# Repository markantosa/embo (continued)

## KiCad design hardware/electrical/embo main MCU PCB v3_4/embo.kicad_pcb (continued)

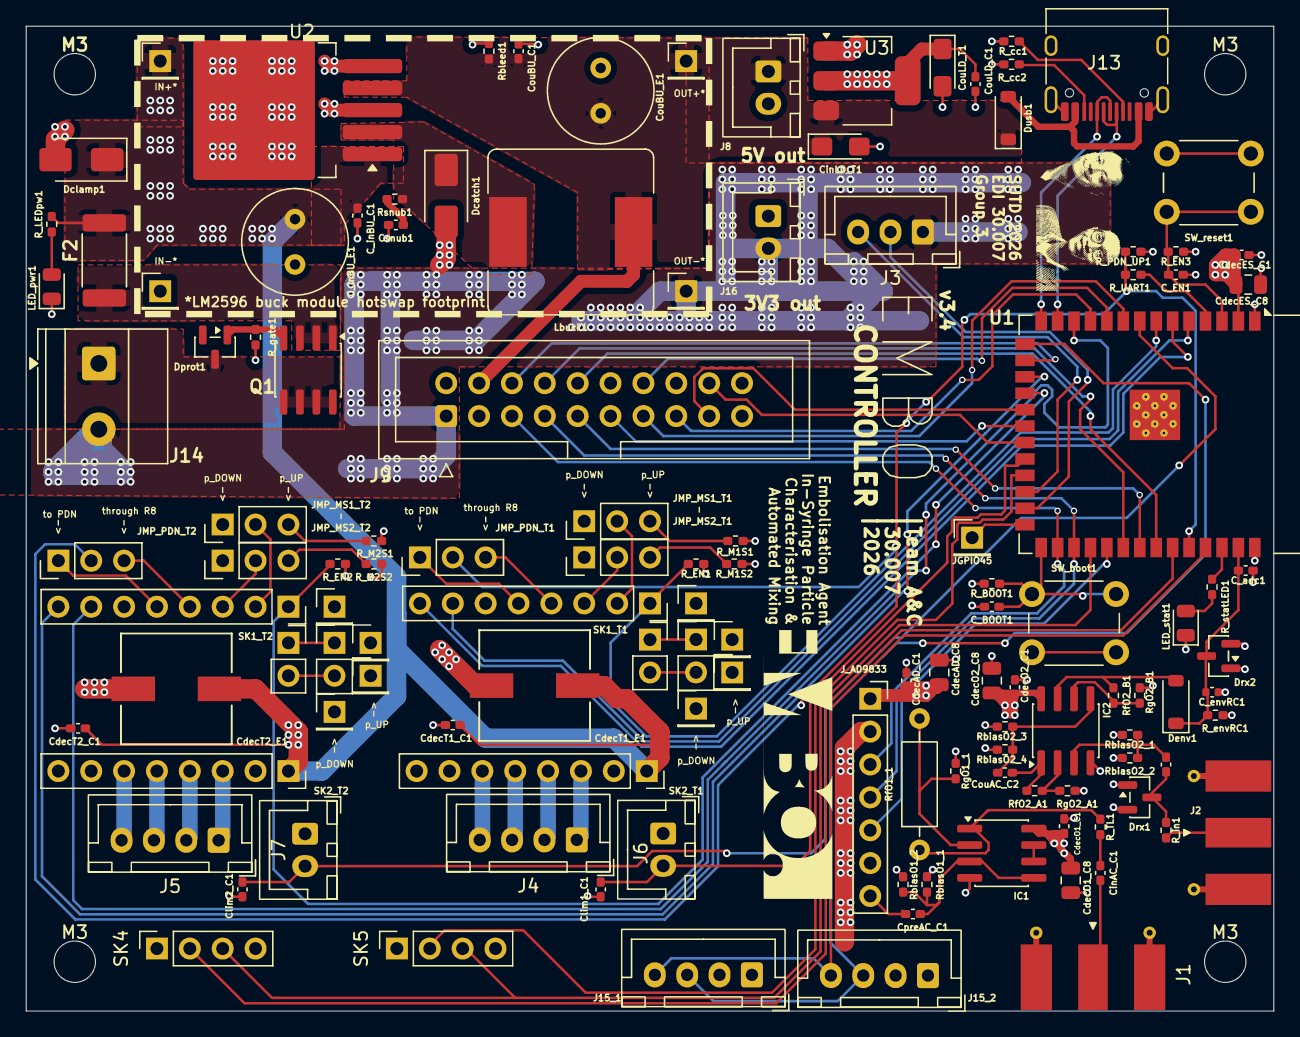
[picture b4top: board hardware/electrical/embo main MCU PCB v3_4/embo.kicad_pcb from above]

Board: 4 copper layers, 96.4 x 76.1 mm, 125 parts (0 on the bottom side), 90 nets.

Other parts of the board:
M3, M3#2, M3#3, M3#4: MountingHole_3.2mm_M3

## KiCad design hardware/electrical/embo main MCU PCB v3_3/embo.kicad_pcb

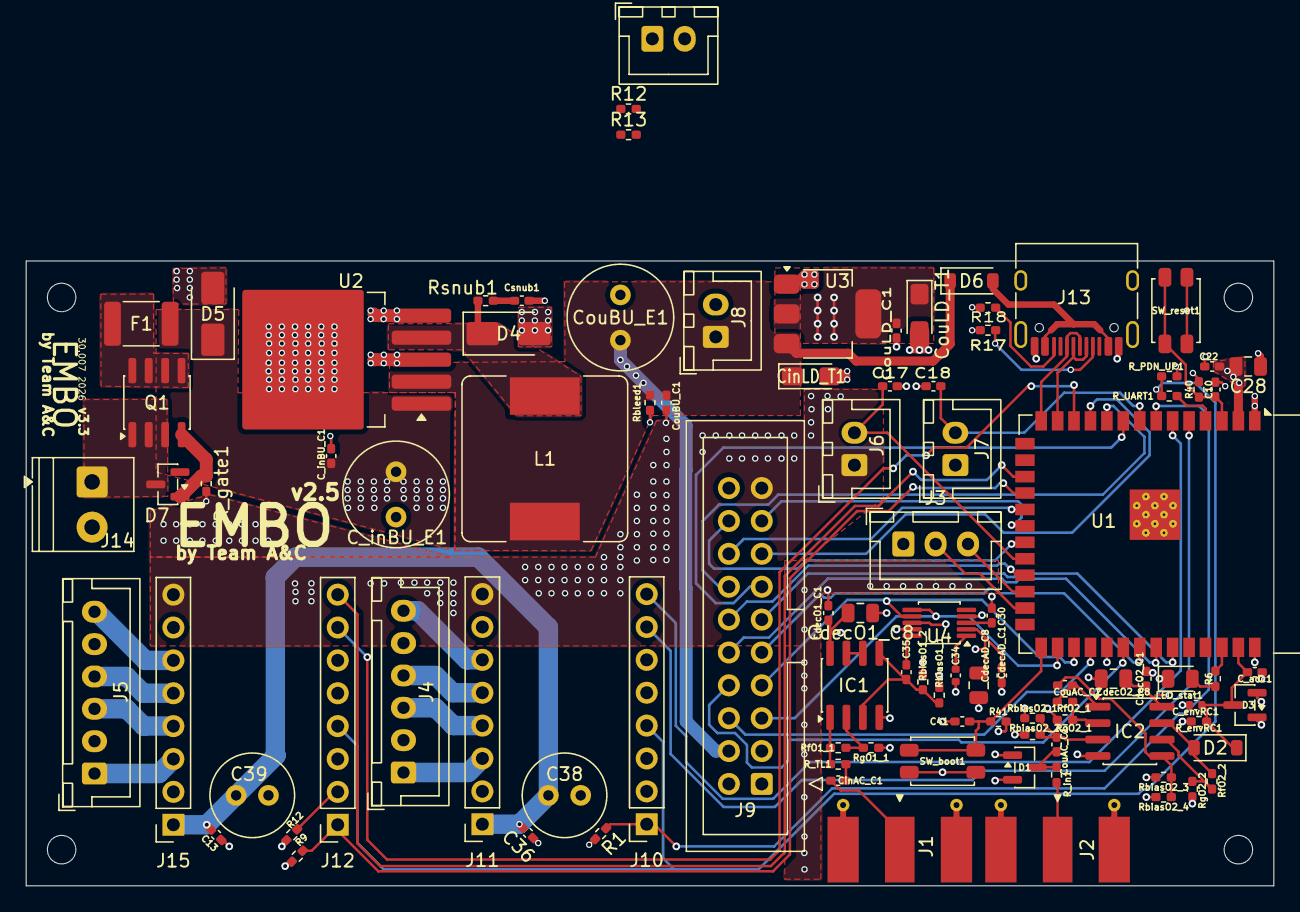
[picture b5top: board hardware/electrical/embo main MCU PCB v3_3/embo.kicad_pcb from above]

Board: 4 copper layers, 96.4 x 48.3 mm, 97 parts (0 on the bottom side), 72 nets.

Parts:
C10: 1µF X7R; C_0402_1005Metric_Pad0.74x0.62mm_HandSolder
C13, C17, C18, C22, C30, C35, C36, C41: 100nF X7R; C_0402_1005Metric_Pad0.74x0.62mm_HandSolder
C28: 10µF X5R 0805; C_0805_2012Metric
C34: 10nF X7R; C_0402_1005Metric
C38, C39: 100µF 35V electrolytic radial; C_Radial_D6.3mm_H7.0mm_P2.50mm
C_adc1: 100nF X7R; C_0402_1005Metric_Pad0.74x0.62mm_HandSolder
C_envRC1: 10nF X7R; C_0402_1005Metric
C_inBU_C1: 100nF X7R; C_0402_1005Metric_Pad0.74x0.62mm_HandSolder
C_inBU_E1: 100 µF 50 V radial; C_Radial_D8.0mm_H11.5mm_P3.50mm
CdecAD_C1: 100nF X7R; C_0402_1005Metric_Pad0.74x0.62mm_HandSolder
CdecAD_C8: 10µF X5R 0805; C_0805_2012Metric
CdecO1_C1, CdecO2_C1: 100nF X7R; C_0402_1005Metric_Pad0.74x0.62mm_HandSolder
CdecO1_C8, CdecO2_C8: 10µF X5R 0805; C_0805_2012Metric
CinAC_C1: 100nF X7R; C_0402_1005Metric_Pad0.74x0.62mm_HandSolder
CinLD_T1: 10µF 10V tantalum Case A; CP_EIA-3216-18_Kemet-A_HandSolder
CouAC_C1, CouAC_C2: 100nF X7R; C_0402_1005Metric_Pad0.74x0.62mm_HandSolder
CouBU_C1: 100nF X7R; C_0402_1005Metric_Pad0.74x0.62mm_HandSolder
CouBU_E1: 220µF 10V low-ESR electrolytic radial; C_Radial_D8.0mm_H11.5mm_P3.50mm
CouLD_C1: 100nF X7R; C_0402_1005Metric_Pad0.74x0.62mm_HandSolder
CouLD_T1: 10µF 10V tantalum Case A; CP_EIA-3216-18_Kemet-A_HandSolder
Csnub1: 1nF X7R; C_0402_1005Metric_Pad0.74x0.62mm_HandSolder
D1, D3: BAV99; SOT-23
D2: BAT54; D_SOD-123
D4: SS34A; D_SMA
D5: SMBJ28A; D_SMA
D6: 1N5819; D_SOD-123
D7: BZX84C15, 15 V Zener, SOT-23; SOT-23
F1: 5A littlefuse; Fuse_1812_4532Metric_Pad1.30x3.40mm_HandSolder
IC1, IC2: OPA2354; SOIC-8_3.9x4.9mm_P1.27mm
J1, J2: Conn_Coaxial; SMA_Molex_73251-1153_EdgeMount_Horizontal
J3: UART to RPi; JST_XH_B3B-XH-A_1x03_P2.50mm_Vertical
J4: JSTXH 6pin Socket 1; JST_XH_B6B-XH-A_1x06_P2.50mm_Vertical
J5: JSTXH 6pin Socket 2; JST_XH_B6B-XH-A_1x06_P2.50mm_Vertical
J6: motor 1; JST_XH_B2B-XH-A_1x02_P2.50mm_Vertical
J7: motor 2; JST_XH_B2B-XH-A_1x02_P2.50mm_Vertical
J8: 5V out; JST_XH_B2B-XH-A_1x02_P2.50mm_Vertical
J8#2: LED Panel; JST_XH_B2B-XH-A_1x02_P2.50mm_Vertical
J9: Conn_02x10_Odd_Even; IDC-Header_2x10_P2.54mm_Vertical
J10, J11, J12, J15: Conn_01x08; PinSocket_1x08_P2.54mm_Vertical
J13: USB_C_Receptacle_USB2.0_16P; USB_C_Receptacle_HRO_TYPE-C-31-M-12
J14: 24 V PSU input; TerminalBlock_Phoenix_PT-1,5-2-3.5-H_1x02_P3.50mm_Horizontal
L1: 100µH; L_Bourns_SRR1260
LED_stat1: green LED; LED_0805_2012Metric
Q1: AO4407A; SOIC-8_3.9x4.9mm_P1.27mm
R1, R9, R12, R12#2, R13: 10kΩ; R_0402_1005Metric_Pad0.72x0.64mm_HandSolder
R6: 330Ω; R_0402_1005Metric_Pad0.72x0.64mm_HandSolder
R17, R18: 5.1kΩ; R_0402_1005Metric_Pad0.72x0.64mm_HandSolder
R40, R41: 10kΩ 0402; R_0402_1005Metric_Pad0.72x0.64mm_HandSolder
R_PDN_UP1: 10kΩ 0402; R_0402_1005Metric_Pad0.72x0.64mm_HandSolder
R_TL1: 47Ω; R_0402_1005Metric_Pad0.72x0.64mm_HandSolder
R_UART1: 1kΩ 0402; R_0402_1005Metric_Pad0.72x0.64mm_HandSolder
R_envRC1: 10kΩ 0402; R_0402_1005Metric_Pad0.72x0.64mm_HandSolder
R_gate1: 10 kΩ 0402; R_0402_1005Metric_Pad0.72x0.64mm_HandSolder
R_in1: 100Ω 0402; R_0402_1005Metric_Pad0.72x0.64mm_HandSolder
RbiasO1_1, RbiasO1_2, RbiasO2_1, RbiasO2_2, RbiasO2_3, RbiasO2_4: 10kΩ; R_0402_1005Metric_Pad0.72x0.64mm_HandSolder
Rbleed1: 4.7kΩ; R_0402_1005Metric_Pad0.72x0.64mm_HandSolder
RfO1_1: 390Ω; R_0402_1005Metric_Pad0.72x0.64mm_HandSolder
RfO2_1, RfO2_2: 910Ω; R_0402_1005Metric_Pad0.72x0.64mm_HandSolder
RgO1_1, RgO2_1, RgO2_2: 100Ω; R_0402_1005Metric_Pad0.72x0.64mm_HandSolder
Rsnub1: 10kΩ; R_0402_1005Metric_Pad0.72x0.64mm_HandSolder
SW_boot1: 6×6mm tactile; SW_SPST_EVQP2_MiddlePushTravel_H2.5mm
SW_reset1: 6×6mm tactile; SW_SPST_EVQP2_MiddlePushTravel_H2.5mm
U1: ESP32-S3-WROOM-1
U2: LM2596S-5; TO-263-5_TabPin3
U3: AMS1117-3.3; SOT-223-3_TabPin2
U4: AD9833xRM; MSOP-10_3x3mm_P0.5mm

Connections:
+3V3: C22.2, C28.2, CdecAD_C1.1, CdecAD_C8.2, CdecO1_C1.1, CdecO1_C8.1, CdecO2_C1.1, CdecO2_C8.1, CouLD_C1.1, CouLD_T1.1, D1.2 (A), D3.2 (A), IC1.8 (V+), IC2.8 (V+), J9.2, J11.7, J15.7, R1.1, R9.1, R12.1, R12#2.1, R13.1, R40.2, R41.2, R_PDN_UP1.2, RbiasO1_1.1, RbiasO2_1.1, RbiasO2_3.1, U1.2 (3V3), U3.2 (VO), U4.2 (VDD)
+5V: CinLD_T1.1, CouBU_C1.1, CouBU_E1.1, D6.1 (K), J8.1, J8#2.1, J9.4, L1.1, Rbleed1.1, U2.4 (FB), U3.3 (VI)
+24V: C13.1, C36.1, C38.1, C39.1, C_inBU_C1.1, C_inBU_E1.1, D5.1 (K), F1.2, J11.1, J15.1, U2.1 (VIN)
/AD9833_SC: U1.31 (IO38), U4.8 (~FSYNC)
/BTN1: J9.16, U1.19 (IO11)
/BTN2: J9.17, U1.20 (IO12)
/BUZ_PWM: J9.18, U1.21 (IO13)
/EC11_A (CLK): J9.13, U1.9 (IO16)
/EC11_B (DT): J9.14, U1.10 (IO17)
/EC11_SW: J9.15, U1.11 (IO18)
/LIMIT_M1: C17.1, J6.2, U1.22 (IO14)
/LIMIT_M2: C18.1, J7.2, U1.8 (IO15)
/M1_A1: J4.3, J11.4
/M1_A2: J4.1, J11.3
/M1_B1: J4.4, J11.5
/M1_B2: J4.6, J11.6
/M1_DIR: J10.8, U1.6 (IO6)
/M1_EN: J10.1, R1.2, U1.7 (IO7)
/M1_STEP: J10.7, U1.5 (IO5)
/M2_A1: J5.3, J15.4
/M2_A2: J5.1, J15.3
/M2_B1: J5.4, J15.5
/M2_B2: J5.6, J15.6
/M2_DIR: J12.8, U1.17 (IO9)
/M2_EN: J12.1, R9.2, U1.18 (IO10)
/M2_STEP: J12.7, U1.12 (IO8)
/RX_AMP_IN: CouAC_C1.1, D1.3 (K), R_in1.2
/SPI_CLK: J9.7, U1.29 (IO36), U4.7 (SCLK)
/SPI_MISO: J9.6, U1.30 (IO37)
/SPI_MOSI: J9.5, U1.28 (IO35), U4.6 (SDATA)
/STAGE1_OUT: CouAC_C2.1, IC2.1 (OUTA), RfO2_1.2
/TFT_CS: J9.8, U1.32 (IO39)
/TFT_DC: J9.9, U1.33 (IO40)
/TFT_RST: J9.10, U1.34 (IO41)
/TMC_UART: R_UART1.2, U1.4 (IO4)
/TOUCH_CS: J9.11, U1.35 (IO42)
/TOUCH_IRQ: J9.12, U1.23 (IO21)
/TX_AMP_IN: C35.1, U4.10 (VOUT)
/TX_OUT: CinAC_C1.2, J1.1 (In)
/UART_RX: J3.2, U1.25 (IO48)
/UART_TX: J3.3, U1.24 (IO47)
/UAS_ADC: C_adc1.1, C_envRC1.1, D2.1 (K), D3.3 (K), R_envRC1.1, U1.39 (IO1)
/USB_D+: J13.A6 (D+), J13.B6 (D+), U1.14 (USB_D+)
/USB_D-: J13.A7 (D-), J13.B7 (D-), U1.13 (USB_D-)
/status_LED: R6.2, U1.38 (IO2)
GND: C10.2, C13.2, C17.2, C18.2, C22.1, C28.1, C30.2, C34.1, C36.2, C38.2, C39.2, C41.2, C_adc1.2, C_envRC1.2, C_inBU_C1.2, C_inBU_E1.2, CdecAD_C1.2, CdecAD_C8.1, CdecO1_C1.2, CdecO1_C8.2, CdecO2_C1.2, CdecO2_C8.2, CinLD_T1.2, CouBU_C1.2, CouBU_E1.2, CouLD_C1.2, CouLD_T1.2, Csnub1.2, D1.1 (K), D3.1 (K), D4.2 (A), D5.2 (A), IC1.4 (V-), IC2.4 (V-), J1.2 (Ext), J2.2 (Ext), J3.1, J6.1, J7.1, J8.2, J8#2.2, J9.1, J9.3, J9.19, J10.3, J10.6, J11.2, J11.8, J12.3, J12.6, J13.A1 (GND), J13.A12 (GND), J13.B1 (GND), J13.B12 (GND), J13.SH (SHIELD), J14.2, J15.2, J15.8, LED_stat1.1 (K), R17.2, R18.2, R_envRC1.2, R_gate1.2, RbiasO1_2.2, RbiasO2_2.2, RbiasO2_4.2, Rbleed1.2, RgO1_1.1, RgO2_1.1, RgO2_2.2, SW_boot1.2, SW_reset1.2, U1.1 (GND), U1.40 (GND), U1.41 (GND), U2.3 (GND), U2.5 (~ON/OFF), U3.1 (GND), U4.4 (DGND), U4.9 (AGND)
unnamed: CinAC_C1.1, R_TL1.2
unnamed: Csnub1.1, Rsnub1.2
unnamed: D2.2 (A), IC2.7 (OUTB), RfO2_2.2
unnamed: D4.1 (K), L1.2, Rsnub1.1, U2.2 (OUT)
unnamed: D6.2 (A), J13.A4 (VBUS), J13.A9 (VBUS), J13.B4 (VBUS), J13.B9 (VBUS)
unnamed: D7.1 (A), Q1.4, R_gate1.1
unnamed: D7.3 (K), J14.1, Q1.5, Q1.6, Q1.7, Q1.8
unnamed: F1.1, Q1.1, Q1.2, Q1.3
unnamed: C35.2, IC1.3 (+INA), IC1.5 (+INB), RbiasO1_1.2, RbiasO1_2.1
unnamed: IC1.2 (-INA), RfO1_1.2, RgO1_1.2
unnamed: IC1.6 (-INB), IC1.7 (OUTB)
unnamed: IC1.1 (OUTA), R_TL1.1, RfO1_1.1
unnamed: CouAC_C1.2, IC2.3 (+INA), RbiasO2_1.2, RbiasO2_2.1
unnamed: CouAC_C2.2, IC2.5 (+INB), RbiasO2_3.2, RbiasO2_4.1
unnamed: IC2.2 (-INA), RfO2_1.1, RgO2_1.2
unnamed: IC2.6 (-INB), RfO2_2.1, RgO2_2.1
unnamed: J2.1 (In), R_in1.1
unnamed: J12.2, R12#2.2
unnamed: J13.A5 (CC1), R17.1
unnamed: J13.B5 (CC2), R18.1
unnamed: R_PDN_UP1.1, R_UART1.1
unnamed: LED_stat1.2 (A), R6.1
unnamed: C10.1, R40.1, SW_reset1.1, U1.3 (EN)
unnamed: C41.1, R41.1, SW_boot1.1, U1.27 (IO0)
unnamed: C30.1, U4.3 (CAP/2.5V)
unnamed: C34.2, U4.1 (COMP)

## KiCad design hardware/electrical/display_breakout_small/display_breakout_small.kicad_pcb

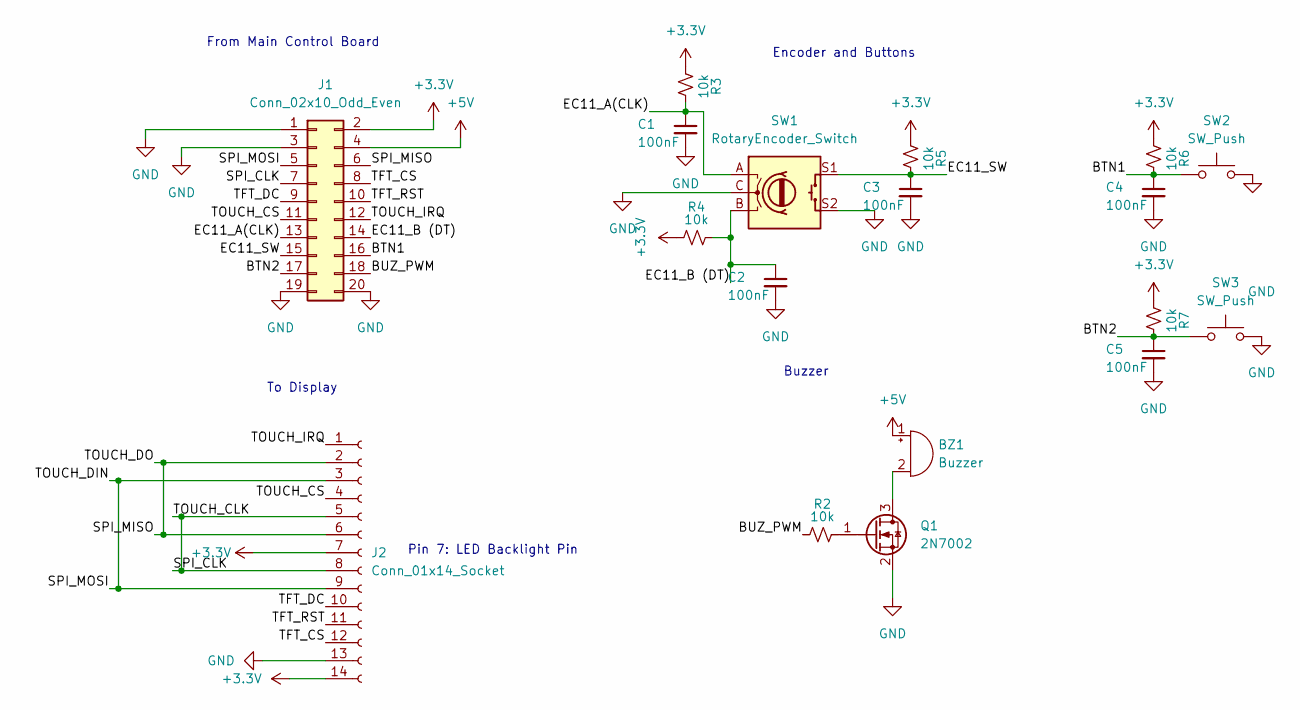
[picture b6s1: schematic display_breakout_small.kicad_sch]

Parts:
BZ1: Buzzer; Buzzer_12x9.5RM7.6
C1, C2, C3, C4, C5: 100nF; C_0402_1005Metric_Pad0.74x0.62mm_HandSolder
J1: Conn_02x10_Odd_Even; IDC-Header_2x10_P2.54mm_Vertical
J2: Conn_01x14_Socket; PinSocket_1x14_P2.54mm_Vertical
Q1: 2N7002; SOT-23
R2, R3, R4, R5, R6, R7: 10k; R_0402_1005Metric_Pad0.72x0.64mm_HandSolder
SW1: RotaryEncoder_Switch; RotaryEncoder_Alps_EC11E-Switch_Vertical_H20mm
SW2, SW3: SW_Push; SW_TH_Tactile_Omron_B3F-100x

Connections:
+3.3V: J1.2, J2.7, J2.14, R3.2, R4.2, R5.2, R6.2, R7.2
+5V: BZ1.1 (+), J1.4
/BTN1: C4.1, J1.16, R6.1, SW2.1
/BTN2: C5.1, J1.17, R7.1, SW3.1
/BUZ_PWM: J1.18, R2.2
/EC11_A(CLK): C1.1, J1.13, R3.1, SW1.A
/EC11_B (DT): C2.1, J1.14, R4.1, SW1.B
/EC11_SW: C3.1, J1.15, R5.1, SW1.S1
/SPI_CLK: J1.7, J2.5, J2.8
/SPI_MISO: J1.6, J2.2, J2.6
/SPI_MOSI: J1.5, J2.3, J2.9
/TFT_CS: J1.8, J2.12
/TFT_DC: J1.9, J2.10
/TFT_RST: J1.10, J2.11
/TOUCH_CS: J1.11, J2.4
/TOUCH_IRQ: J1.12, J2.1
GND: C1.2, C2.2, C3.2, C4.2, C5.2, J1.1, J1.3, J1.19, J1.20, J2.13, Q1.2 (S), SW1.C, SW1.S2, SW2.2, SW3.2
unnamed: BZ1.2 (-), Q1.3 (D)
unnamed: Q1.1 (G), R2.1

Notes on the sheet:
Buzzer
From Main Control Board
Encoder and Buttons
Pin 7: LED Backlight Pin
To Display

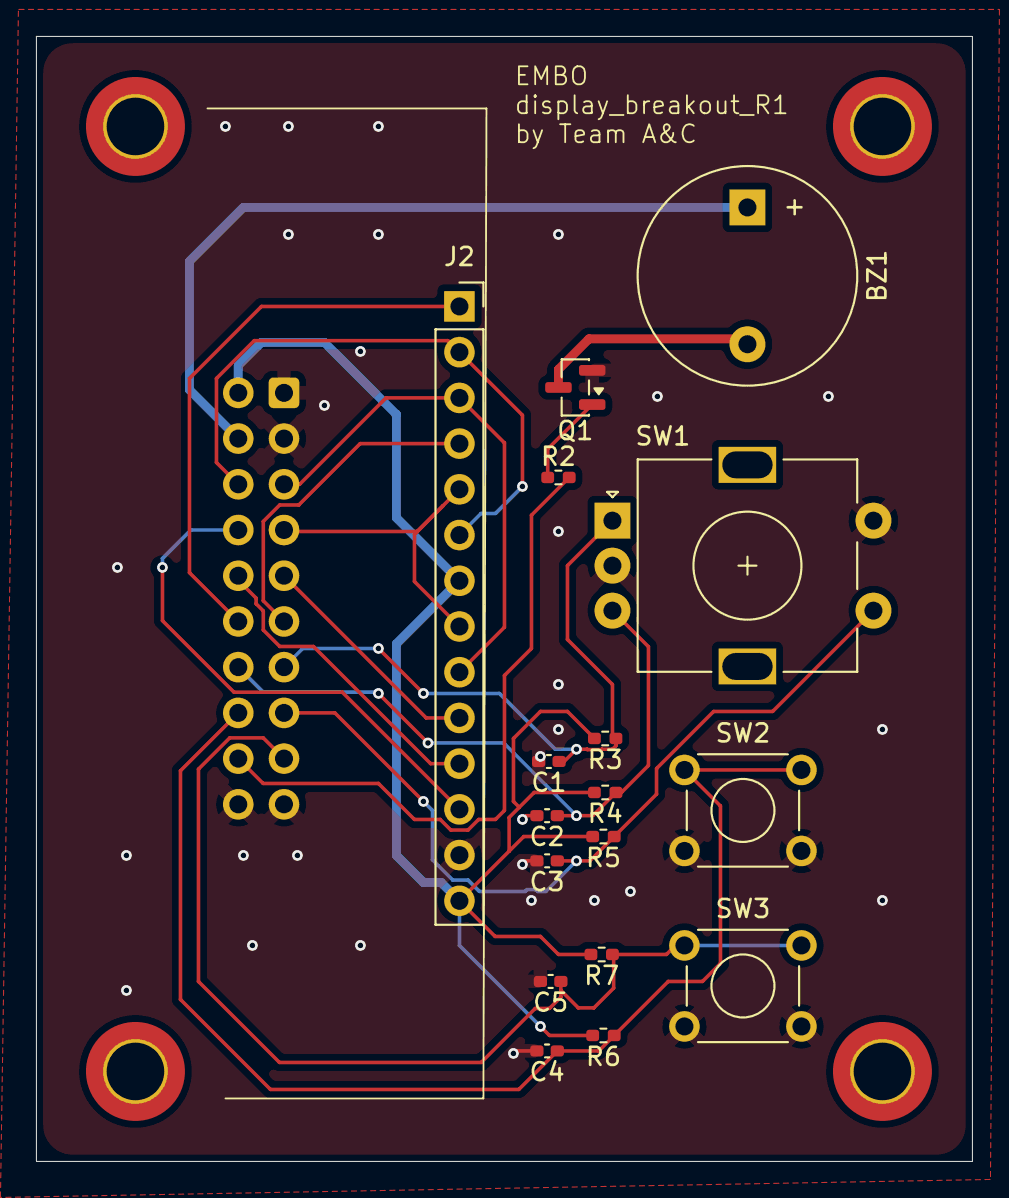
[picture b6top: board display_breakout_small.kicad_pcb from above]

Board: 2 copper layers, 52.0 x 62.5 mm, 18 parts (1 on the bottom side), 19 nets.

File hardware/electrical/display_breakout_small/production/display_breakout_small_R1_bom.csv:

Designator,Footprint,Quantity,Value,LCSC Part #
BZ1,Buzzer_12x9.5RM7.6,1,Buzzer,
"C1, C2, C3, C4, C5",0402,5,100nF,
J1,IDC-Header_2x10_P2.54mm_Vertical,1,Conn_02x10_Odd_Even,
J2,PinSocket_1x14_P2.54mm_Vertical,1,Conn_01x14_Socket,
Q1,SOT-23,1,2N7002,
"R2, R3, R4, R5, R6, R7",0402,6,10k,
SW1,RotaryEncoder_Alps_EC11E-Switch_Vertical_H20mm,1,RotaryEncoder_Switch,
"SW2, SW3",SW_TH_Tactile_Omron_B3F-100x,2,SW_Push,

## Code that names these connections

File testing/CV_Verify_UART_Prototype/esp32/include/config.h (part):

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// now two separate pins (GPIO4 TX / GPIO44 RX), not one bidirectional pin.

// UAS / ADC
#define PIN_UAS_ADC         1   // ADC1_CH0 — envelope detector output

// Status LED
#define PIN_STATUS_LED      2

// I2C turbidity bus — APDS9960 (0x39, ALS) + MAX30102 (0x57, backscatter)
#define PIN_I2C_SDA         3
#define PIN_I2C_SCL         43
#define I2C_CLOCK_HZ        400000
#define APDS9960_ADDR       0x39
#define MAX30102_ADDR       0x57
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#define TURBIDITY_REINIT_INTERVAL_MS  2000

// Motor driver — shared PDN_UART bus, genuinely separate TX/RX pins
#define PIN_TMC_UART_TX     4
#define PIN_TMC_UART_RX     44

// Motor 1 (TMC2209 U5/SK1, UART addr set via MS1/MS2 jumpers)
#define PIN_STEP_M1         5
#define PIN_DIR_M1          6
#define PIN_EN_M1           7

// Motor 2 (TMC2209 U6/SK2)
#define PIN_STEP_M2         8
#define PIN_DIR_M2          9
#define PIN_EN_M2           10

// UI buttons (via IDC ribbon)
#define PIN_BTN1            11  // dedicated stop/e-stop button — see ui.h
// GPIO12 = T_CS (touch), not a button as of v3.3 — see below
#define PIN_BUZ_PWM         13  // LEDC PWM → buzzer

// Limit switches
#define PIN_LIMIT_M1        14
#define PIN_LIMIT_M2        15

// EC11 rotary encoder (via IDC ribbon)
#define PIN_EC11_A          16
#define PIN_EC11_B          17
#define PIN_EC11_SW         18

// USB (fixed PHY — do not reassign)
// GPIO19 = USB D−, GPIO20 = USB D+

// Load cells — HX711 x2, shared clock (added v3.2)
#define PIN_HX711_2_DT      21  // CHANGED v3.2: was TOUCH_IRQ pre-v3.2
#define PIN_HX711_SCK       37  // CHANGED v3.2: was SPI_MISO pre-v3.2, shared between both modules
#define PIN_HX711_1_DT      42  // CHANGED v3.2: was TOUCH_CS pre-v3.2

// SPI bus (shared: ILI9341, XPT2046 touch, AD9833) — no MISO on this bus as
// of v3.2 (touch MISO/T_DO moved to GPIO46, see below); AD9833 has no MISO.
#define PIN_SPI_MOSI        35
#define PIN_SPI_CLK         36

// SPI chip selects
#define PIN_AD9833_CS       38  // AD9833 FSYNC — SPI Mode 2
#define PIN_TFT_CS          39  // ILI9341 CS   — SPI Mode 0
#define PIN_TFT_DC          40
#define PIN_TFT_RST         41

// Touch (XPT2046), restored v3.3 on the two remaining strapping pins with
// headroom — see design brief §8.3 for the rationale. T_IRQ is NOT wired on
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// made and reverted after it caused a boot hang — see LGFX_Config.h's
// TOUCH_TODO comment for what to restore once that's debugged on real
// hardware. Currently unused.
#define PIN_TOUCH_CS        12  // T_CS
#define PIN_TOUCH_DO        46  // T_DO (MISO)

// RPi UART (UART1)
#define PIN_RPI_TX          47
#define PIN_RPI_RX          48

// ── SPI clock speeds ─────────────────────────────────────────────────────────
#define SPI_CLK_TFT         20000000   // 20 MHz max via IDC ribbon
#define SPI_CLK_TOUCH        2000000   // 2 MHz (XPT2046 max) — currently unused, see PIN_TOUCH_CS above
#define SPI_CLK_AD9833      10000000   // ~10 MHz — short direct trace

// ── UART speeds ───────────────────────────────────────────────────────────────
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
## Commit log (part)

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2026-06-26 added experimental testing folder
2026-06-27 kicad pcb file
2026-06-27 updated pcb schematic
2026-06-28 Move KiCad project folder under hardware/electrical
2026-06-28 schematic and pcb docs update
2026-06-29 update schematic and PCb docs
2026-06-29 Pinout Cheat Sheet and Firmware Stubs (with rj's UI breakout board idea)
2026-06-29 PCB Placement Update
2026-06-29 updated loadcell testing firmware
2026-06-30 Created display_breakout kicad file folder
2026-06-30 PCB layout update
2026-06-30 Updated breakout schematic
2026-06-30 git test
2026-06-30 git test 2
2026-06-30 included buzzer in schematic
2026-06-30 git test 5
2026-06-30 updated buzzer
2026-06-30 git issue resolution
2026-06-30 update PCB doc for TMC2209 modules instead of QFC-28
2026-06-30 updated schematic to latest version
2026-06-30 updated pcb layout
2026-06-30 updated display_breakout pcb layout
2026-06-30 main PCB layout update
2026-06-30 add firmware todo list, flash guide in readme, TMC motor driver firmware complete
2026-06-30 update all readmes and RPI UART firmware
